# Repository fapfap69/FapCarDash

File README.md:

FapCarDash
==========

A Carputer project made with Arduino and RaspberryPi harware

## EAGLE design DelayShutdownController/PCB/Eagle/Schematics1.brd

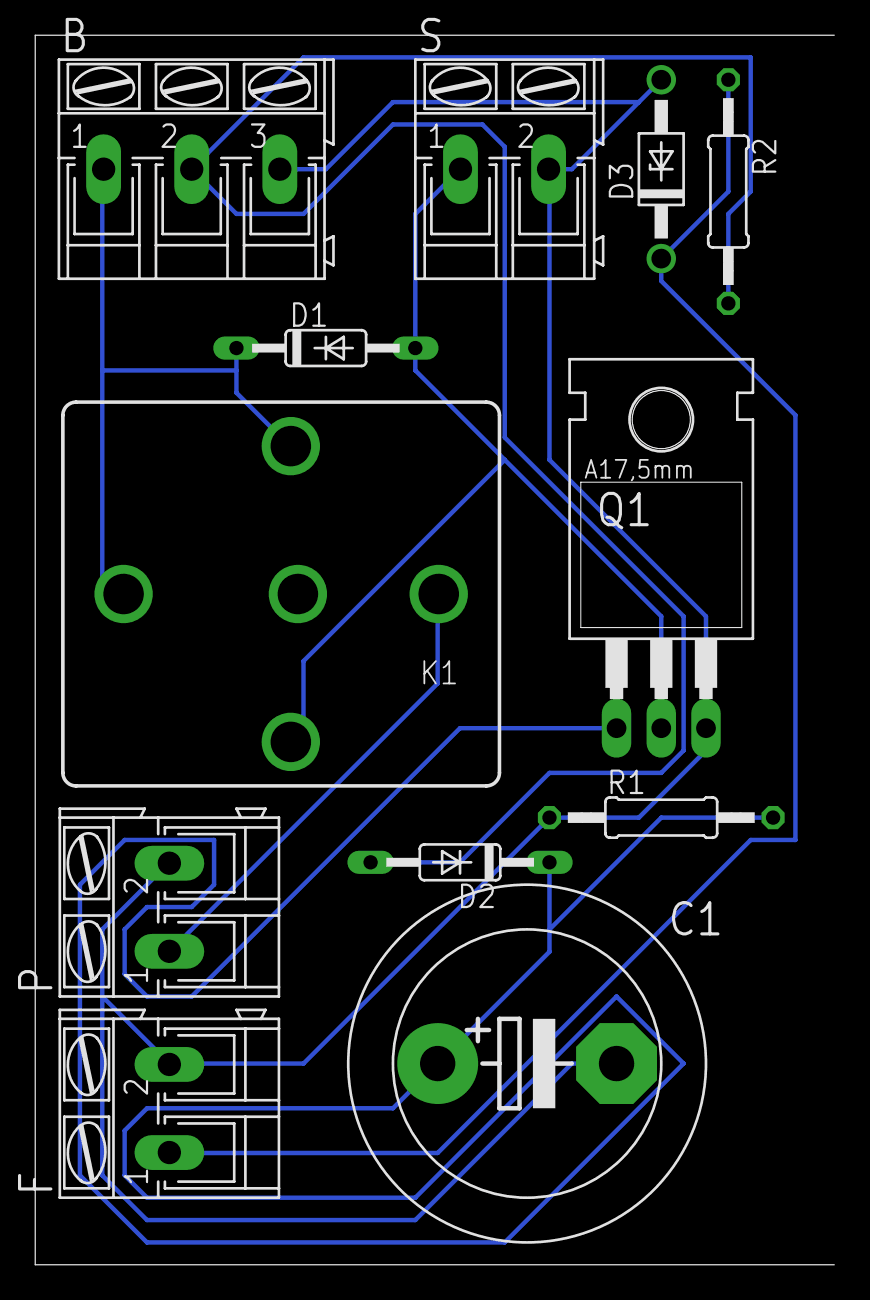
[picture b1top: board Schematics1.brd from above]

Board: 2 copper layers, 45.4 x 69.8 mm, 12 parts (0 on the bottom side), 7 nets.

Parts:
B: BATT; AK300/3
C1: 1mF; EB20D
D1, D2: 1N4148DO35-10; DO35-10
D3: 1N4728; DO41Z10
F: PwFail; AK300/2
K1: CB1A-P-12V; CB1
P: PW; AK300/2
Q1: IRFZ48Z; TO220BH
R1: 100K; 0207/12
R2: 330; 0207/12
S: PWOn; AK300/2

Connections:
+12V: B.1, D1.C, K1.30, K1.85
GND: B.3, C1.-, D3.A, F.2, P.2, Q1.S, R1.1, S.2
unnamed: D3.C, F.1, R2.1
unnamed: C1.+, D2.C, Q1.G, R1.2
unnamed: B.2, D2.A, R2.2
unnamed: K1.87, P.1
unnamed: D1.A, K1.86, Q1.D, S.1

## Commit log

2013-10-24 Second commit
2013-10-25 terzo commit
2013-10-31 Quarto Commit
2013-11-06 Ver 0.1
    Collector funzionante : Arduino + GPSD
2013-11-12 versione con Maps , SetUp e Dash
2013-11-21 Versione con Dash, Map, Calendario Meteo e Setup
